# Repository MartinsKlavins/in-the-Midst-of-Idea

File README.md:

# in-the-Midst-of-Idea
My repository for small or unfinished projects

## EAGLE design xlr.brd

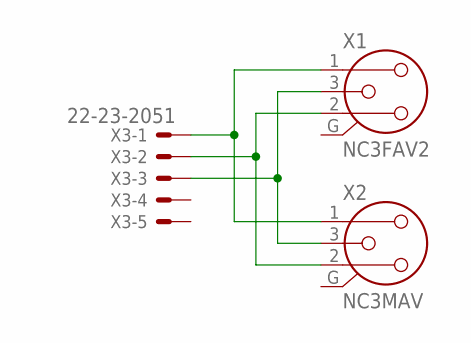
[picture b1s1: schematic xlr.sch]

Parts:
X1: NC3FAV2
X2: NC3MAV
X3: 22-23-2051

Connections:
unnamed: X1.1, X2.1, X3.1
unnamed: X1.2, X2.2, X3.2
unnamed: X1.3, X2.3, X3.3

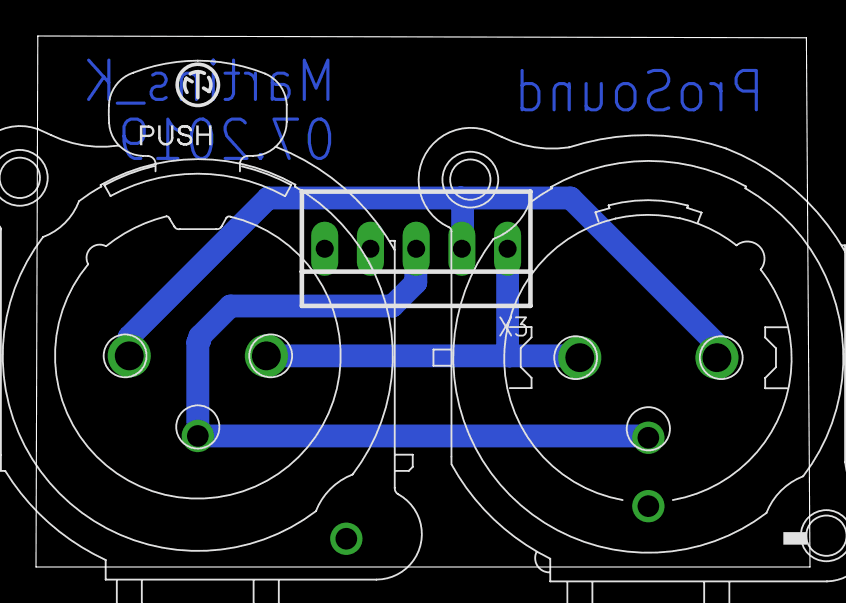
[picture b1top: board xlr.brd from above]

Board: 2 copper layers, 43.0 x 29.5 mm, 3 parts (0 on the bottom side), 3 nets.

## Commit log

2021-02-08 Rename pir.py to PIR audio trigger/pir.py
2021-02-08 Rename eagle.epf to ROBE-LEDBeam150-XLR_PCB/eagle.epf
2021-02-08 Rename xlr.brd to ROBE-LEDBeam150-XLR_PCB/xlr.brd
2021-02-08 Rename xlr.sch to ROBE-LEDBeam150-XLR_PCB/xlr.sch
2021-02-10 Rename readme.txt to README.md
2021-02-10 Rename index.php to WIRELESS fixture for stage lighting/webserver/index.php
2021-02-10 Rename PIR audio trigger/README.md to PIR_Audio_Trigger/README.md
2021-02-10 Rename PIR audio trigger/pir.py to PIR_Audio_Trigger/pir.py
2021-02-10 Rename WIRELESS fixture for stage lighting/webserver/index.php to WIRELESS_fixture_for_stage_lighting/WebServer/index.php
